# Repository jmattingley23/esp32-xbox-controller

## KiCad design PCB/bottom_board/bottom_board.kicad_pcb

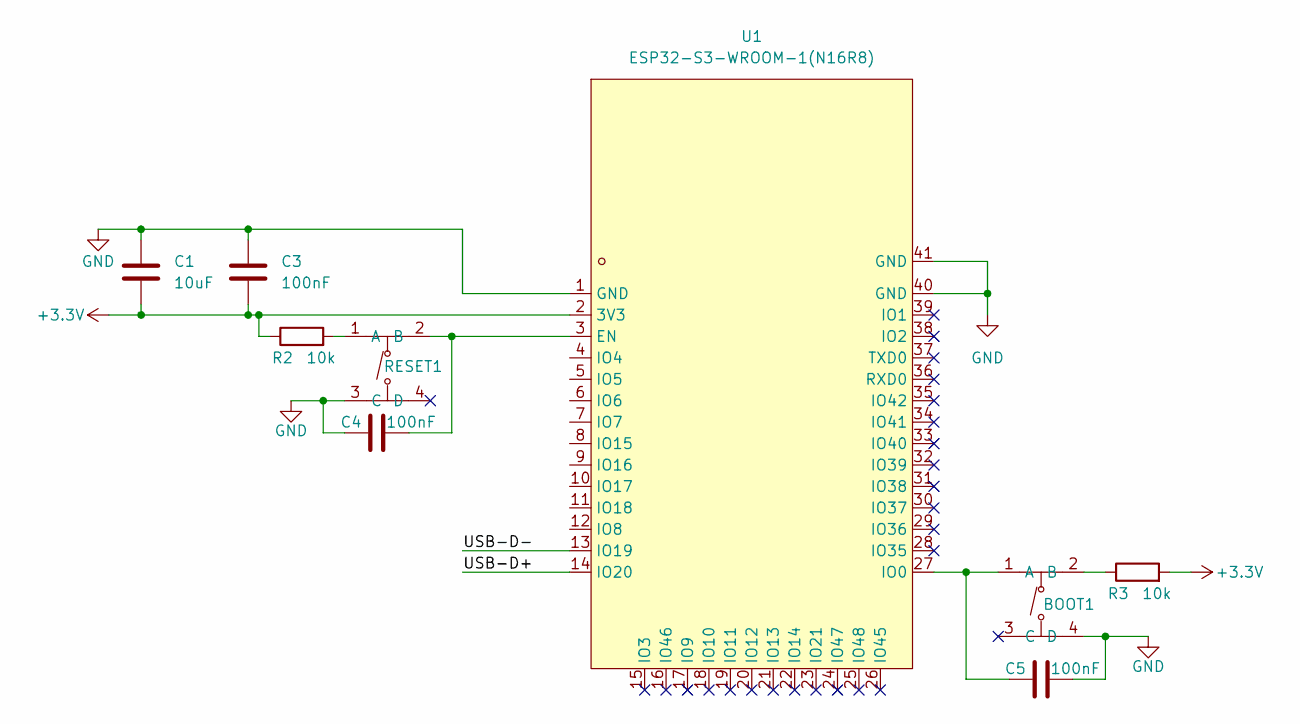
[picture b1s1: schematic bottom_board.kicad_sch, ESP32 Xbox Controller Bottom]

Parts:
BOOT1: TS-1187A-B-A-B; SW-SMD_4P-L5.2-W5.2-P3.70-LS6.4
C1: 10uF; C_0805_2012Metric; LCSC Part C440198
C3, C4, C5: 100nF; C_0402_1005Metric; LCSC Part C307331
R2, R3: 10k; R_0402_1005Metric; LCSC Part C25744
RESET1: TS-1187A-B-A-B; SW-SMD_4P-L5.2-W5.2-P3.70-LS6.4
U1: ESP32-S3-WROOM-1(N16R8); WIRELM-SMD_ESP32-S3-WROOM-1; LCSC Part C2913202

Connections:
+3.3V: C1.2, C3.2, R2.1, R3.2, U1.2 (3V3)
/USB-D+: U1.14 (IO20)
/USB-D-: U1.13 (IO19)
GND: BOOT1.4 (D), C1.1, C3.1, C4.1, C5.2, RESET1.3 (C), U1.1 (GND), U1.40 (GND), U1.41 (GND)
unnamed: BOOT1.1 (A), C5.1, U1.27 (IO0)
unnamed: BOOT1.2 (B), R3.1
unnamed: R2.2, RESET1.1 (A)
unnamed: C4.2, RESET1.2 (B), U1.3 (EN)

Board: 2 copper layers, 9 parts (0 on the bottom side), 6 nets, no tracks yet.

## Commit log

2025-01-19 Initial project setup
2025-01-25 Start schematic
